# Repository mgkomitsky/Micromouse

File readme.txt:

Wichtige Hinweise zu den Nutzungsrechten
____________________________________

Die FAULHABER CAD 3D-Modelle sind eine kostenlose Service-Leistung der
Firma DR. FRITZ  FAULHABER GMBH & CO. KG, 71101 Schönaich (Germany).
Sie dürfen nur vollständig und unverändert genutzt oder weitergegeben werden.
Jegliche Veränderungen sind unzulässig und verstoßen gegen das Urheberrecht.

Alle Abmessungen sind in Millimeter angegeben. Dies muss insbesondere beim Laden
in CAD Systeme berücksichtigt werden, die auf anderen Einheiten basiert sind.
Es muss sichergestellt sein, dass die Abmessungen richtig übernommen werden!
Vor dem Import in die CAD Anwendung Millimeter einstellen!

Diese Zeichnungen sind nur als Hilfsmittel zu verstehen. Sie sind jedoch - insbesondere
in Hinblick auf die Abmessungen und den Lieferumfang - nicht verbindlich und
unterliegen keinem automatischen Änderungsdienst.
Aktuelle Zeichnungen können über das Internet heruntergeladen werden unter:

http://www.faulhaber.com

Wir bemühen uns um ständige Pflege und Verbesserung der Zeichnungen. Dennoch
können wir nicht garantieren, dass sie frei von Fehlern sind.
Die Nutzung der Daten erfolgt daher auf eigene Gefahr.

Durch die Benutzung der Daten erklären Sie sich mit diesen Bestimmungen einverstanden.

(c) Copyright 2013, DR.FRITZ FAULHABER GMBH & CO.KG.
Alle Rechte vorbehalten.

Conditions of Use
____________________________________

The FAULHABER CAD 3D-Drawings are a free service of
DR. FRITZ  FAULHABER GMBH & CO. KG, 71101 Schönaich (Germany).
They may only be used and distributed in a complete and unaltered form.
All copy rights reserved.

Please Note: All dimensions are displayed using the metric system (millimeters). 
Your CAD system maybe preset to another system of measurements or dimenstions.
Preset millimeter in the CAD application before importing the file!

These models are intended as a conceptual aid only. All dimensions are subject 
to change without notice. The most up-to-date drawings can be downloaded 
from the Internet at:

http://www.faulhaber.com

Though we encdeavor to maintain the accuracy of the models provided we can provide 
no guarantee of their accuracy.  Use of the models is at your own risk.

With the use of the data you agree with the aforementioned conditions.

(c) Copyright 2013, DR.FRITZ FAULHABER GMBH & CO.KG.
All rights reserved.

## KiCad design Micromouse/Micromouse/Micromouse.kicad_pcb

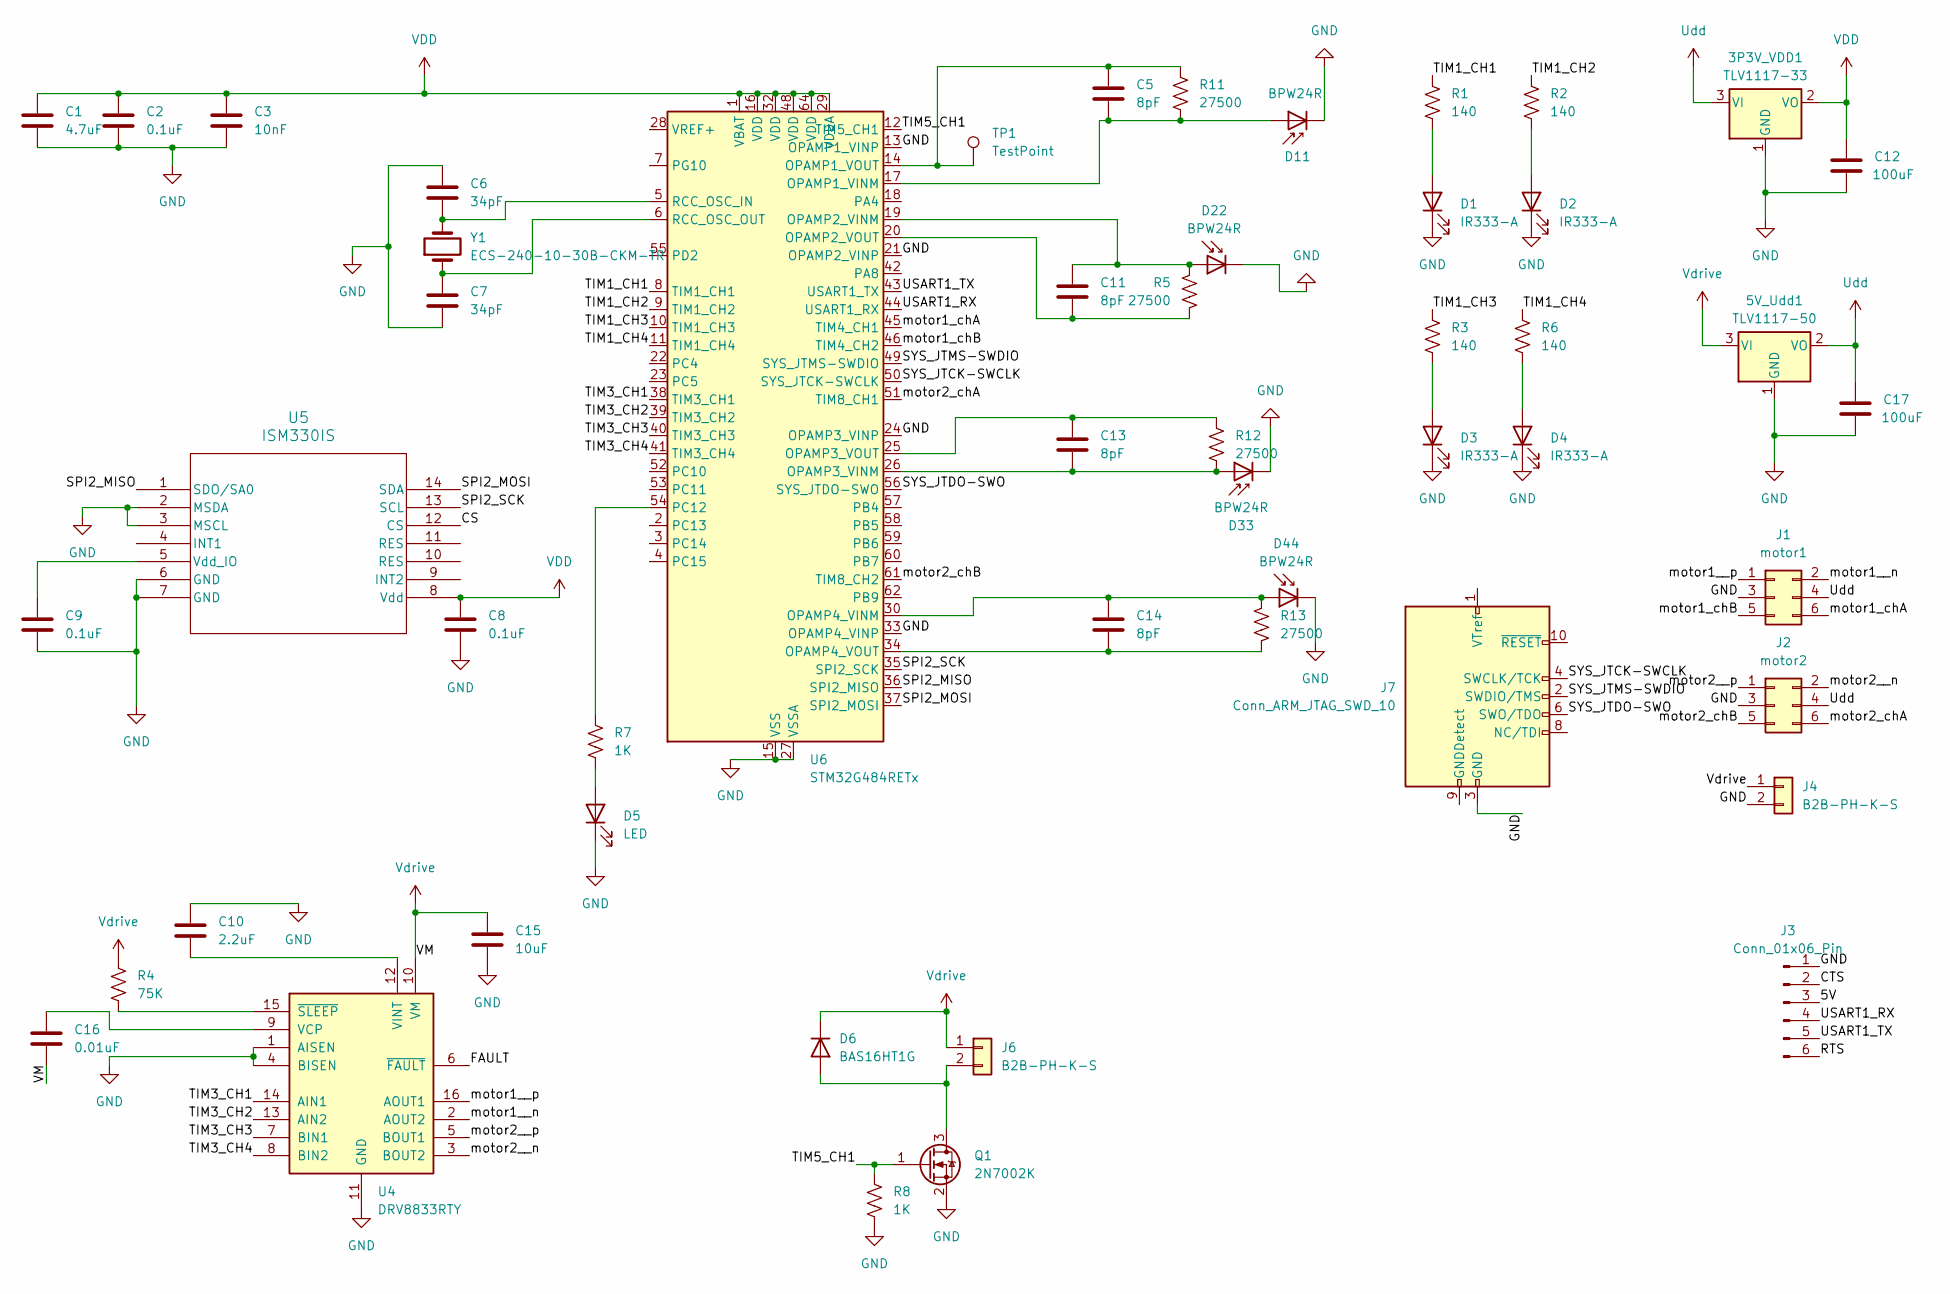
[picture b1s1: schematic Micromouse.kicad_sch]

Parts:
3P3V_VDD1: TLV1117-33; WSON-8-1EP_4x4mm_P0.8mm_EP2.2x3mm_ThermalVias
5V_Udd1: TLV1117-50; WSON-8-1EP_4x4mm_P0.8mm_EP2.2x3mm_ThermalVias
C1: 4.7uF; C_0805_2012Metric
C2, C8, C9: 0.1uF; C_0805_2012Metric
C3: 10nF; C_0805_2012Metric
C5, C11, C13, C14: 8pF; C_0805_2012Metric
C6, C7: 34pF; C_0805_2012Metric
C10: 2.2uF; C_0805_2012Metric
C12, C17: 100uF; C_0805_2012Metric
C15: 10uF; C_0805_2012Metric
C16: 0.01uF; C_0805_2012Metric
D1, D2, D3, D4: IR333-A; LED_D5.0mm
D5: LED; LED_0805_2012Metric
D6: BAS16HT1G; D_SOD-323
D11, D22, D33, D44: BPW24R; TO-18-2
J1: motor1; IDC-Header_2x03_P2.54mm_Vertical
J2: motor2; IDC-Header_2x03_P2.54mm_Vertical
J3: Conn_01x06_Pin; PinHeader_1x06_P2.54mm_Vertical
J4, J6: B2B-PH-K-S; JST_PH_B2B-PH-K_1x02_P2.00mm_Vertical
J7: Conn_ARM_JTAG_SWD_10; PinHeader_2x05_P1.27mm_Vertical_SMD
Q1: 2N7002K; SOT-23
R1, R2, R3, R6: 140; R_0805_2012Metric
R4: 75K; R_0805_2012Metric
R5, R11, R12, R13: 27500; R_0805_2012Metric
R7, R8: 1K; R_0805_2012Metric
TP1: TestPoint; PinHeader_1x01_P2.54mm_Vertical
U4: DRV8833RTY; Texas_RTY_WQFN-16-1EP_4x4mm_P0.65mm_EP2.1x2.1mm_ThermalVias
U5: ISM330IS; LGA-14L_2P5X3X0P83_STM
U6: STM32G484RETx; LQFP-64_10x10mm_P0.5mm
Y1: ECS-240-10-30B-CKM-TR; ECX-53BSMD CRYSTAL

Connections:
/5V: J3.3
/CS: U5.12 (CS)
/CTS: J3.2
/FAULT: U4.6 (~FAULT)
/RTS: J3.6
/SPI2_MISO: U5.1 (SDO/SA0), U6.36 (SPI2_MISO)
/SPI2_MOSI: U5.14 (SDA), U6.37 (SPI2_MOSI)
/SPI2_SCK: U5.13 (SCL), U6.35 (SPI2_SCK)
/SYS_JTCK-SWCLK: J7.4 (SWCLK/TCK), U6.50 (SYS_JTCK-SWCLK)
/SYS_JTDO-SWO: J7.6 (SWO/TDO), U6.56 (SYS_JTDO-SWO)
/SYS_JTMS-SWDIO: J7.2 (SWDIO/TMS), U6.49 (SYS_JTMS-SWDIO)
/TIM1_CH1: R1.1, U6.8 (TIM1_CH1)
/TIM1_CH2: R2.1, U6.9 (TIM1_CH2)
/TIM1_CH3: R3.1, U6.10 (TIM1_CH3)
/TIM1_CH4: R6.1, U6.11 (TIM1_CH4)
/TIM3_CH1: U4.14 (AIN1), U6.38 (TIM3_CH1)
/TIM3_CH2: U4.13 (AIN2), U6.39 (TIM3_CH2)
/TIM3_CH3: U4.7 (BIN1), U6.40 (TIM3_CH3)
/TIM3_CH4: U4.8 (BIN2), U6.41 (TIM3_CH4)
/TIM5_CH1: Q1.1 (G), R8.1, U6.12 (TIM5_CH1)
/USART1_RX: J3.4, U6.44 (USART1_RX)
/USART1_TX: J3.5, U6.43 (USART1_TX)
/motor1__n: J1.2, U4.2 (AOUT2)
/motor1__p: J1.1, U4.16 (AOUT1)
/motor1_chA: J1.6, U6.45 (TIM4_CH1)
/motor1_chB: J1.5, U6.46 (TIM4_CH2)
/motor2__n: J2.2, U4.3 (BOUT2)
/motor2__p: J2.1, U4.5 (BOUT1)
/motor2_chA: J2.6, U6.51 (TIM8_CH1)
/motor2_chB: J2.5, U6.61 (TIM8_CH2)
GND: 3P3V_VDD1.1 (GND), 5V_Udd1.1 (GND), C1.1, C2.1, C3.1, C6.2, C7.1, C8.1, C9.1, C10.2, C12.1, C15.1, C17.1, D1.1 (K), D2.1 (K), D3.1 (K), D4.1 (K), D5.1 (K), D11.1 (K), D22.1 (K), D33.1 (K), D44.1 (K), J1.3, J2.3, J3.1, J4.2, J7.3 (GND), J7.5 (GND), Q1.2 (S), R8.2, U4.1 (AISEN), U4.4 (BISEN), U4.11 (GND), U4.17 (GND), U5.2 (MSDA), U5.3 (MSCL), U5.6 (GND), U5.7 (GND), U6.13 (OPAMP1_VINP), U6.15 (VSS), U6.21 (OPAMP2_VINP), U6.24 (OPAMP3_VINP), U6.27 (VSSA), U6.31 (VSS), U6.33 (OPAMP4_VINP), U6.47 (VSS), U6.63 (VSS)
unnamed: D1.2 (A), R1.2
unnamed: D2.2 (A), R2.2
unnamed: D3.2 (A), R3.2
unnamed: D4.2 (A), R6.2
unnamed: D5.2 (A), R7.2
unnamed: D6.2 (A), J6.2, Q1.3 (D)
unnamed: C5.1, D11.2 (A), R11.1, U6.17 (OPAMP1_VINM)
unnamed: C11.1, D22.2 (A), R5.1, U6.19 (OPAMP2_VINM)
unnamed: C13.1, D33.2 (A), R12.1, U6.26 (OPAMP3_VINM)
unnamed: C14.1, D44.2 (A), R13.1, U6.30 (OPAMP4_VINM)
unnamed: C16.2, U4.9 (VCP)
unnamed: C10.1, U4.12 (VINT)
unnamed: R4.2, U4.15 (~SLEEP)
unnamed: C9.2, U5.5 (Vdd_IO)
unnamed: C5.2, R11.2, TP1.1, U6.14 (OPAMP1_VOUT)
unnamed: C11.2, R5.2, U6.20 (OPAMP2_VOUT)
unnamed: C13.2, R12.2, U6.25 (OPAMP3_VOUT)
unnamed: C14.2, R13.2, U6.34 (OPAMP4_VOUT)
unnamed: R7.1, U6.54 (PC12)
unnamed: C6.1, U6.5 (RCC_OSC_IN), Y1.2
unnamed: C7.2, U6.6 (RCC_OSC_OUT), Y1.1
Udd: 3P3V_VDD1.3 (VI), 5V_Udd1.2 (VO), C17.2, J1.4, J2.4
VDD: 3P3V_VDD1.2 (VO), C1.2, C2.2, C3.2, C8.2, C12.2, U5.8 (Vdd), U6.1 (VBAT), U6.16 (VDD), U6.29 (VDDA), U6.32 (VDD), U6.48 (VDD), U6.64 (VDD)
Vdrive: 5V_Udd1.3 (VI), C15.2, C16.1, D6.1 (K), J4.1, J6.1, R4.1, U4.10 (VM)

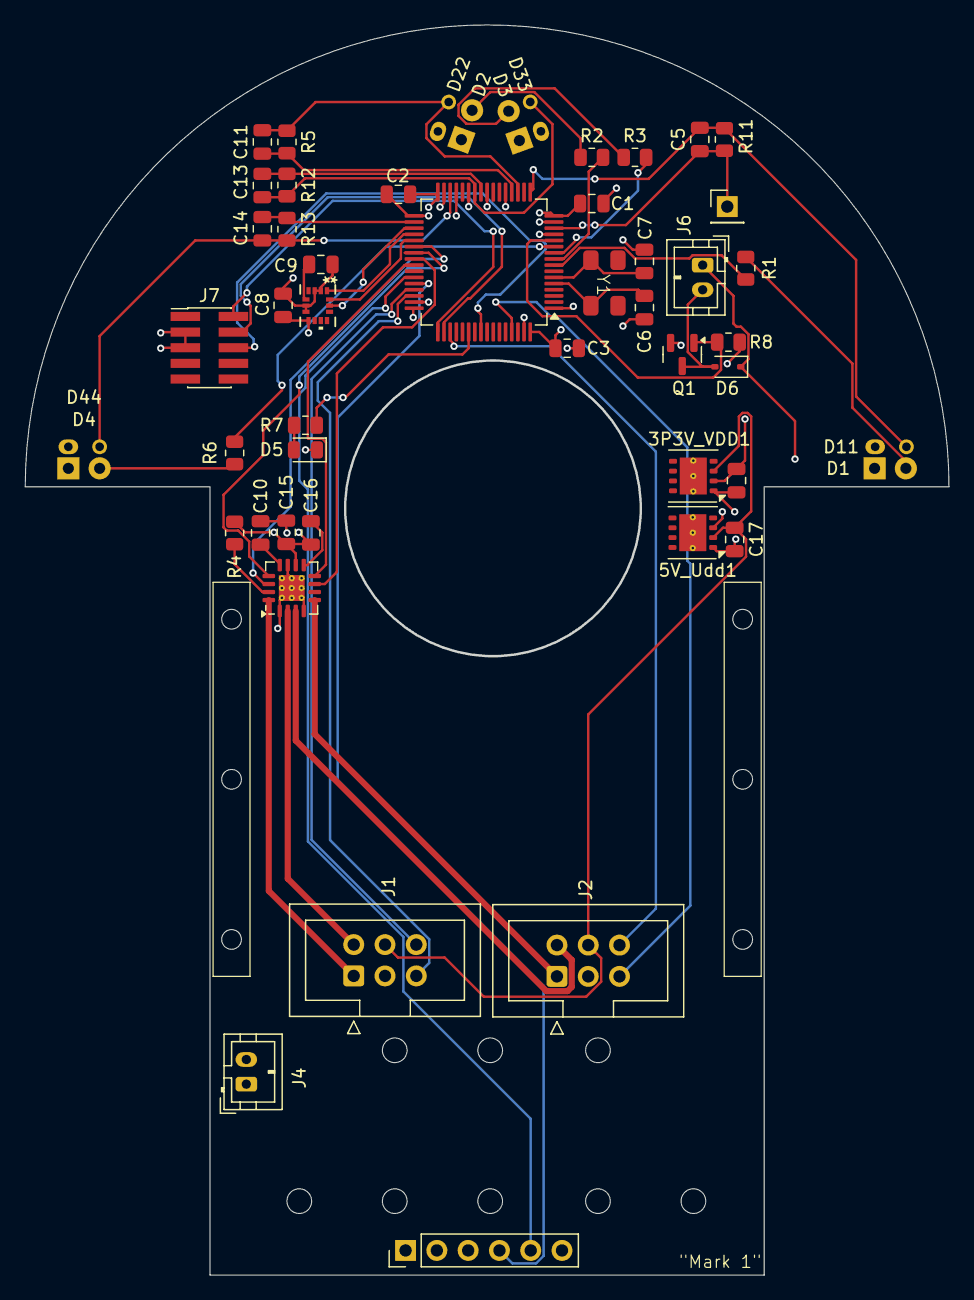
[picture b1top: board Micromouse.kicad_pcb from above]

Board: 4 copper layers, 75.0 x 101.5 mm, 51 parts (0 on the bottom side), 50 nets.

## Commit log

2025-01-04 removed old files
2025-01-04 updated files
2025-01-04 removed backup files
2025-01-04 vdrive trace routing
2025-01-04 silkscreen
